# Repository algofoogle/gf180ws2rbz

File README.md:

# gf180ws2rbz: Raybox-zero supporting materials

For now, this is just a test PCB for various parts that could be used to support a raybox-zero devkit.

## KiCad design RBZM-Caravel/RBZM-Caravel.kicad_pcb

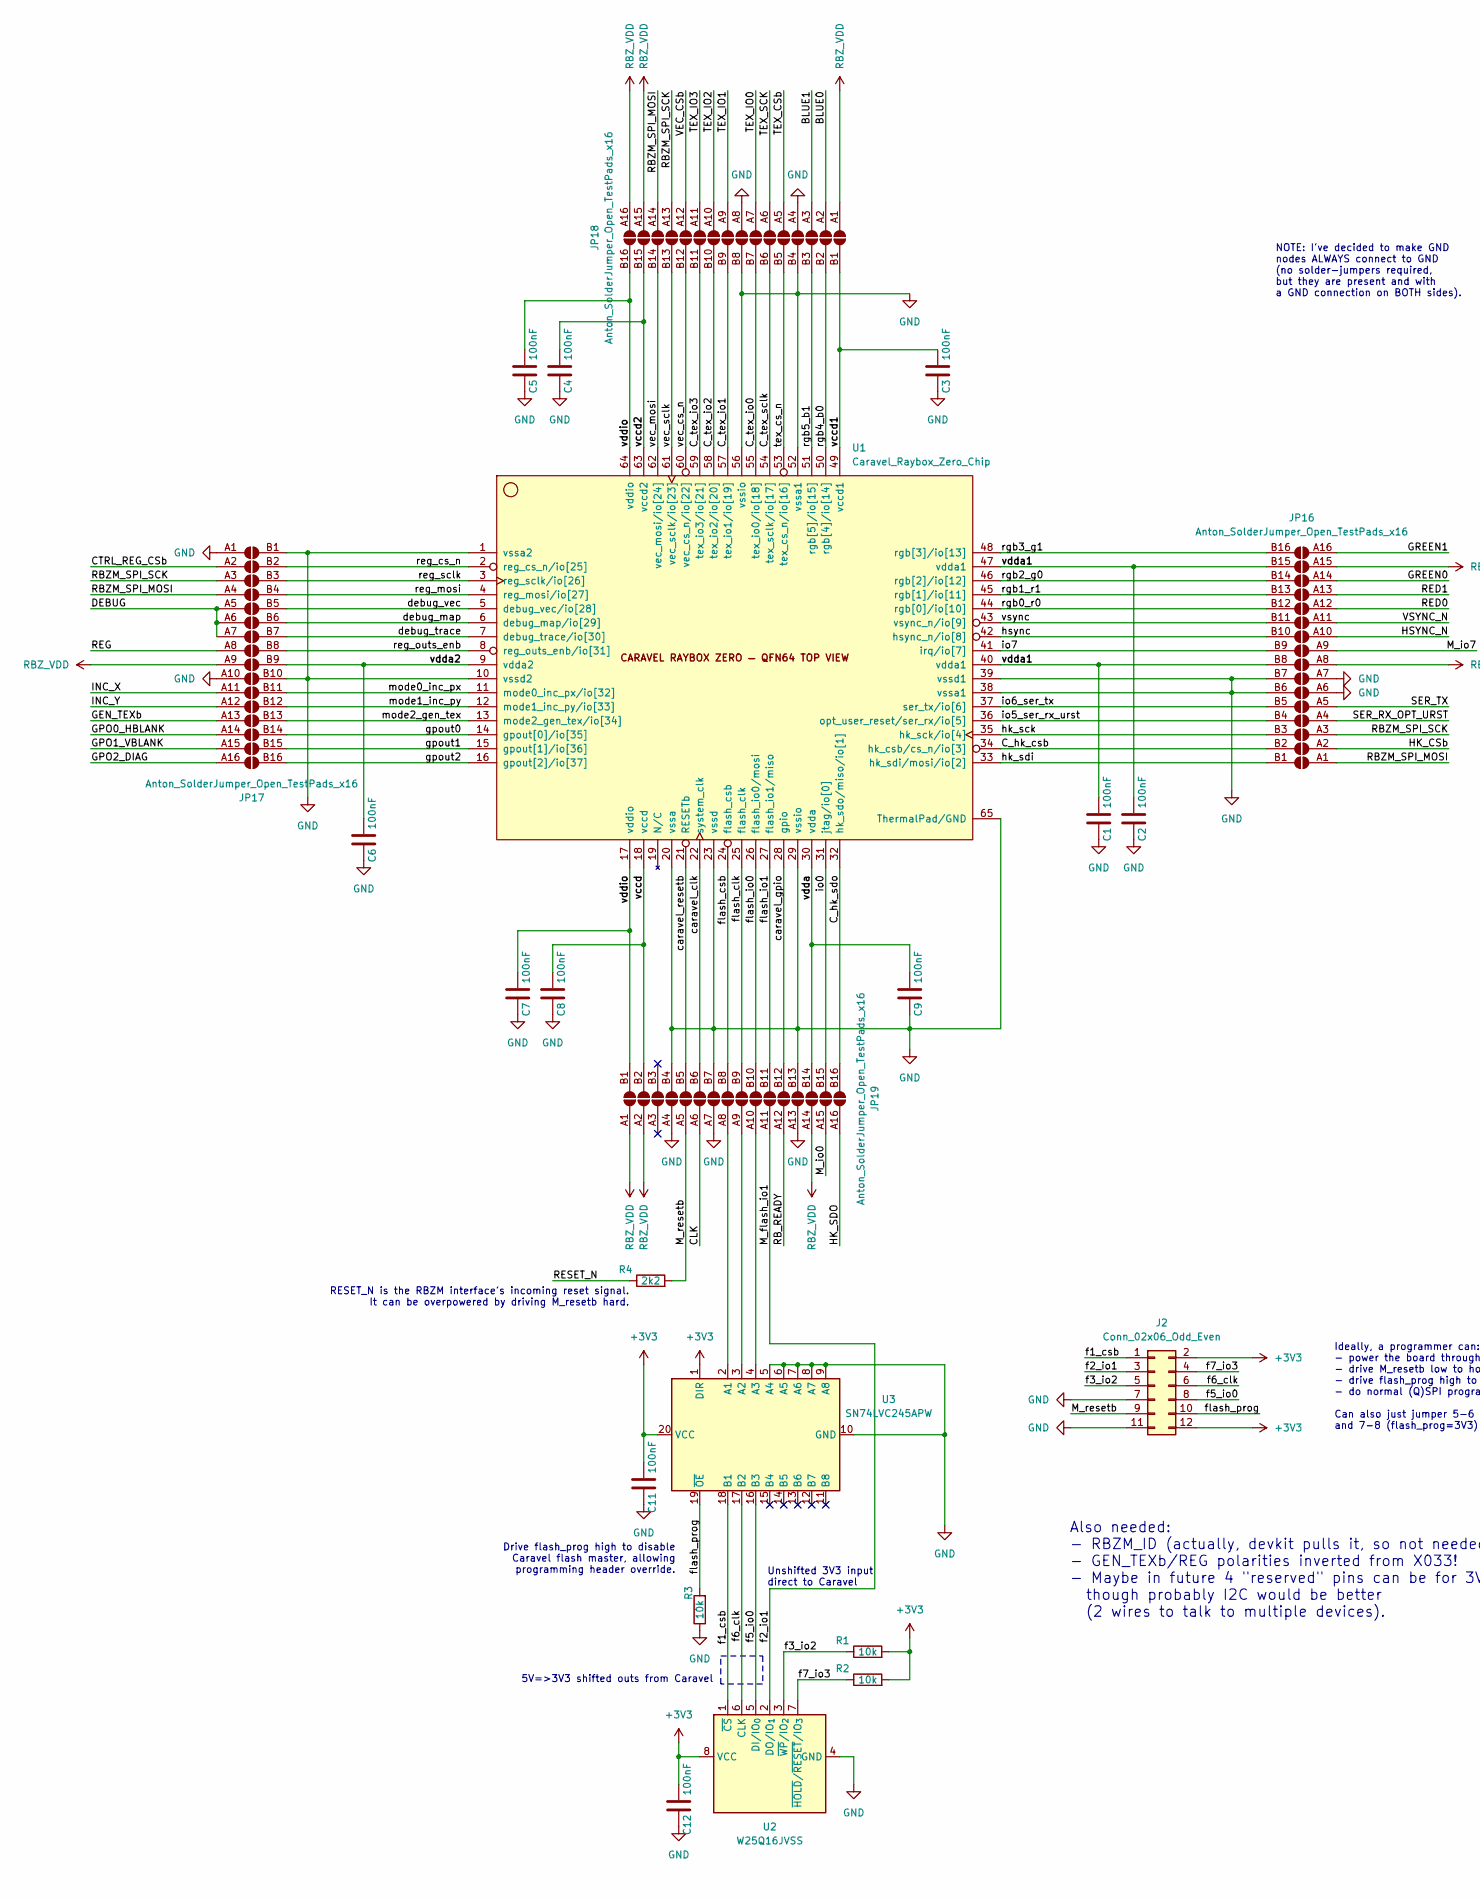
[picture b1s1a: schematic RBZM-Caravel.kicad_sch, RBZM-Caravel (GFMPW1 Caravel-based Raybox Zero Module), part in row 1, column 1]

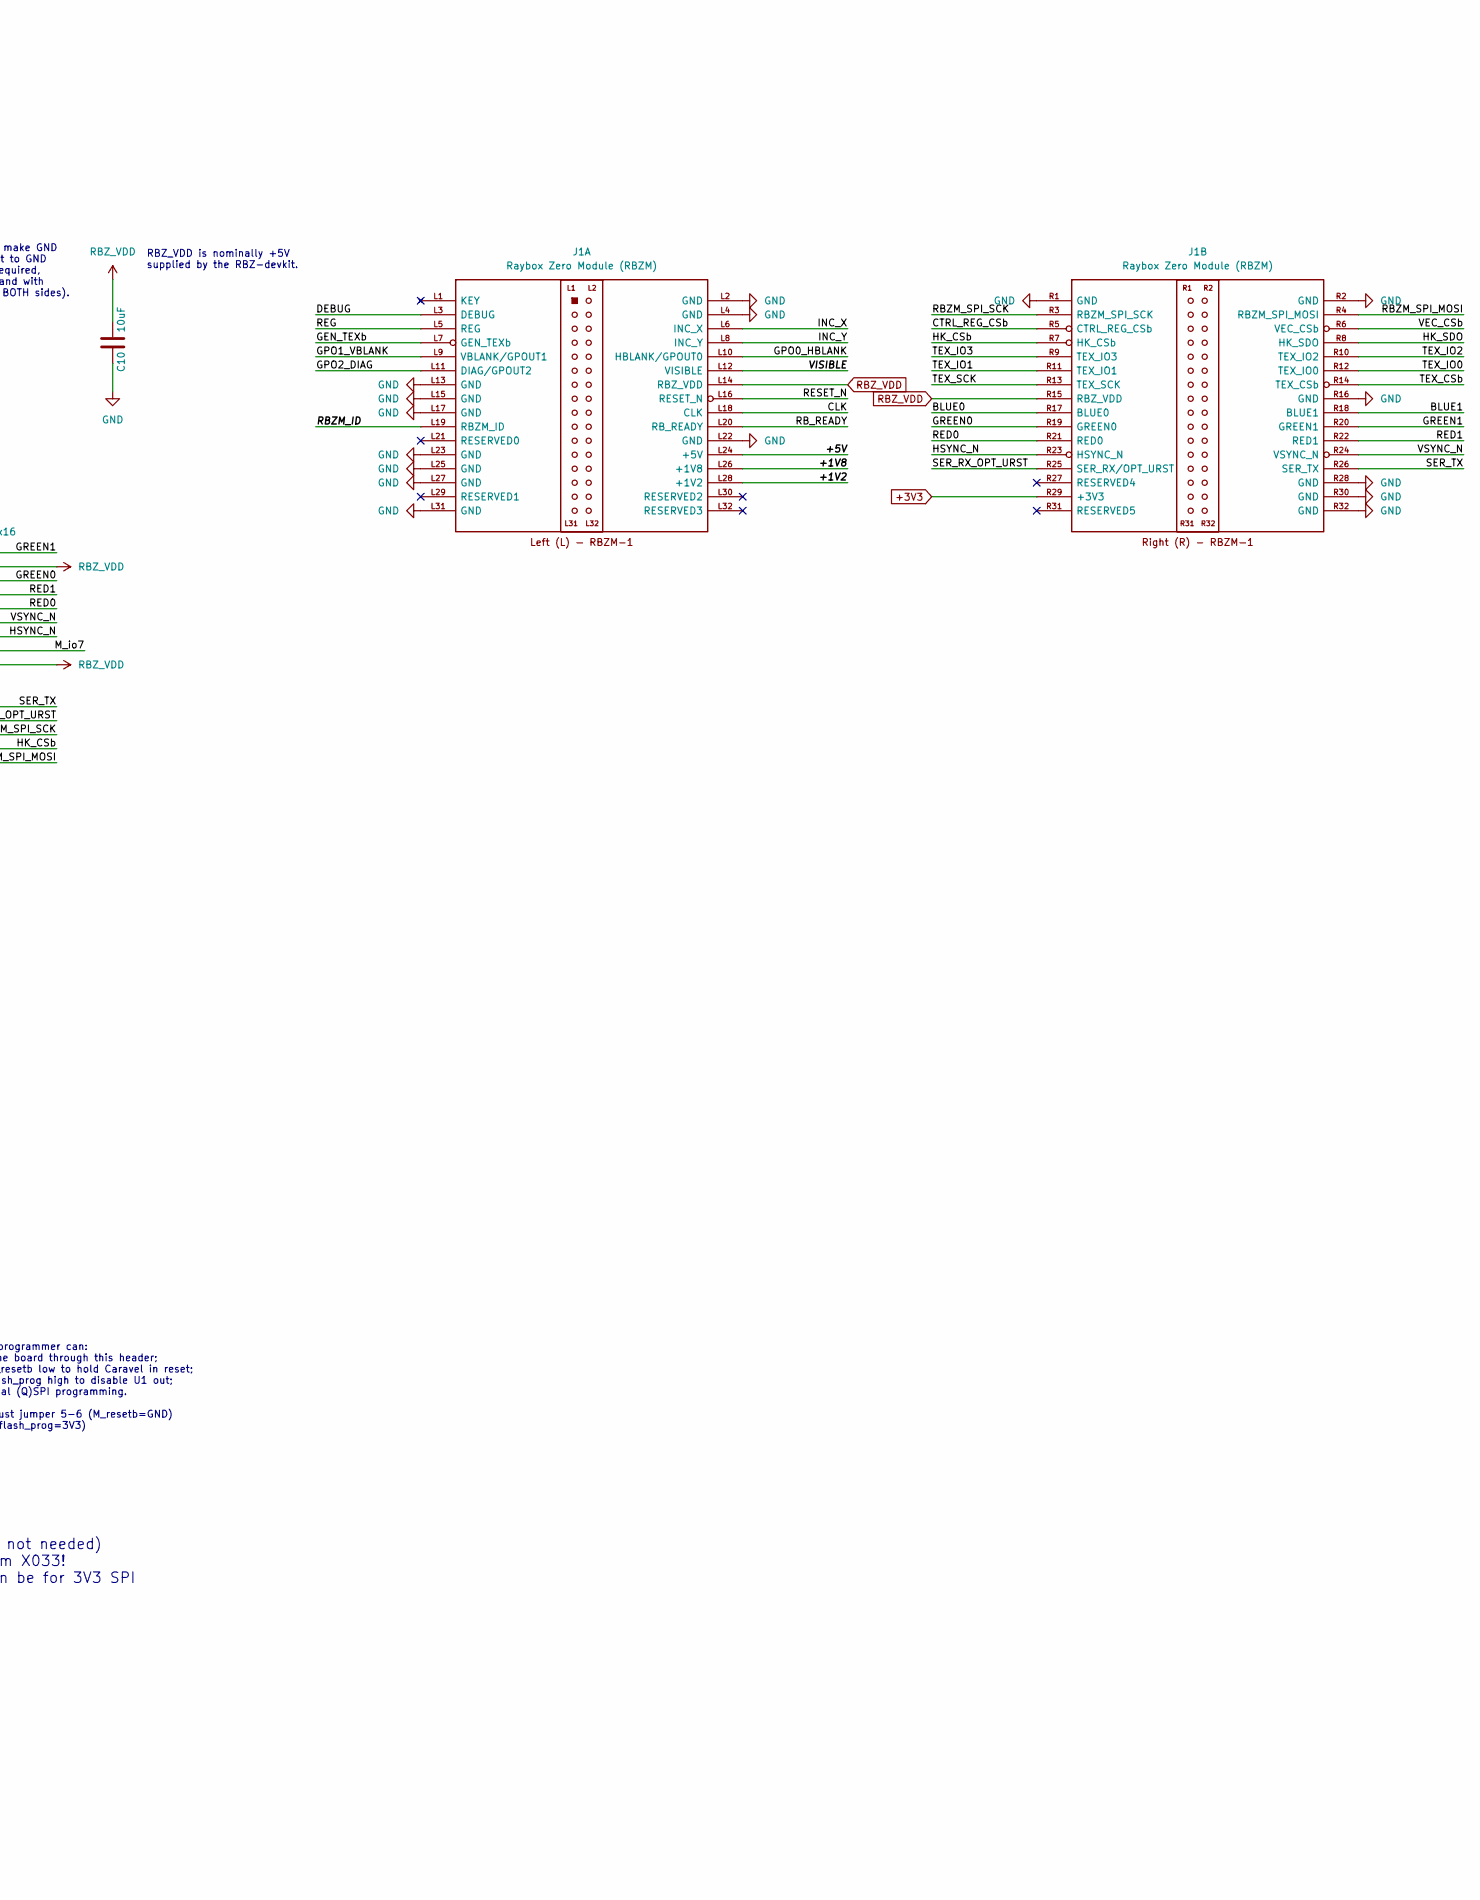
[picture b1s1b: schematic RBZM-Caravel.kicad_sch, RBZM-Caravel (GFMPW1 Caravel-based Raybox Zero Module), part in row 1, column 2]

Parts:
C1, C2, C3, C4, C5, C6, C7, C8, C9, C11, C12: 100nF; C_0603_1608Metric_Pad1.08x0.95mm_HandSolder
C10: 10uF; C_0603_1608Metric_Pad1.08x0.95mm_HandSolder
J1: Raybox Zero Module (RBZM); RBZM_Raybox_Zero_Module
J2: Conn_02x06_Odd_Even; PinHeader_2x06_P2.54mm_Vertical
JP16, JP17, JP18, JP19: Anton_SolderJumper_Open_TestPads_x16; Anton_SolderJumpers_01x16_1.27mm_Compact_SMD
R1, R2, R3: 10k; R_0603_1608Metric_Pad0.98x0.95mm_HandSolder
R4: 2k2; R_0603_1608Metric_Pad0.98x0.95mm_HandSolder
U1: Caravel_Raybox_Zero_Chip; Anton-QFN-64-1EP_9x9mm_P0.5mm_EP7.65x7.65mm-HOLE
U2: W25Q16JVSS; Anton-SOIC-8_MULTIx4.9mm_P1.27mm
U3: SN74LVC245APW; TSSOP-20_4.4x6.5mm_P0.65mm

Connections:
+3V3: C11.2, C12.2, J1.R29 (+3V3), J2.2, J2.12, R1.2, R2.2, U2.8 (VCC), U3.1 (DIR), U3.20 (VCC)
/+1V2: J1.L28 (+1V2)
/+1V8: J1.L26 (+1V8)
/+5V: J1.L24 (+5V)
/BLUE0: J1.R17 (BLUE0), JP18.A2
/BLUE1: J1.R18 (BLUE1), JP18.A3
/CLK: J1.L18 (CLK), JP19.A6
/CTRL_REG_CSb: J1.R5 (CTRL_REG_CSb), JP17.A2
/C_hk_csb: JP16.B2, U1.34 (hk_csb/cs_n/io[3])
/C_hk_sdo: JP19.B16, U1.32 (hk_sdo/miso/io[1])
/C_tex_io0: JP18.B7, U1.55 (tex_io0/io[18])
/C_tex_io1: JP18.B9, U1.57 (tex_io1/io[19])
/C_tex_io2: JP18.B10, U1.58 (tex_io2/io[20])
/C_tex_io3: JP18.B11, U1.59 (tex_io3/io[21])
/C_tex_sclk: JP18.B6, U1.54 (tex_sclk/io[17])
/DEBUG: J1.L3 (DEBUG), JP17.A5, JP17.A6, JP17.A7
/GEN_TEXb: J1.L7 (GEN_TEXb), JP17.A13
/GPO0_HBLANK: J1.L10 (HBLANK/GPOUT0), JP17.A14
/GPO1_VBLANK: J1.L9 (VBLANK/GPOUT1), JP17.A15
/GPO2_DIAG: J1.L11 (DIAG/GPOUT2), JP17.A16
/GREEN0: J1.R19 (GREEN0), JP16.A14
/GREEN1: J1.R20 (GREEN1), JP16.A16
/HK_CSb: J1.R7 (HK_CSb), JP16.A2
/HK_SDO: J1.R8 (HK_SDO), JP19.A16
/HSYNC_N: J1.R23 (HSYNC_N), JP16.A10
/INC_X: J1.L6 (INC_X), JP17.A11
/INC_Y: J1.L8 (INC_Y), JP17.A12
/M_flash_io1: J2.3, JP19.A11, U2.2 (DO/IO_{1})
/M_io0: JP19.A15
/M_io7: JP16.A9
/M_resetb: J2.9, JP19.A5, R4.2
/RBZM_ID: J1.L19 (RBZM_ID)
/RBZM_SPI_MOSI: J1.R4 (RBZM_SPI_MOSI), JP16.A1, JP17.A4, JP18.A14
/RBZM_SPI_SCK: J1.R3 (RBZM_SPI_SCK), JP16.A3, JP17.A3, JP18.A13
/RB_READY: J1.L20 (RB_READY), JP19.A12
/RED0: J1.R21 (RED0), JP16.A12
/RED1: J1.R22 (RED1), JP16.A13
/REG: J1.L5 (REG), JP17.A8
/RESET_N: J1.L16 (RESET_N), R4.1
/SER_RX_OPT_URST: J1.R25 (SER_RX/OPT_URST), JP16.A4
/SER_TX: J1.R26 (SER_TX), JP16.A5
/TEX_CSb: J1.R14 (TEX_CSb), JP18.A5
/TEX_IO0: J1.R12 (TEX_IO0), JP18.A7
/TEX_IO1: J1.R11 (TEX_IO1), JP18.A9
/TEX_IO2: J1.R10 (TEX_IO2), JP18.A10
/TEX_IO3: J1.R9 (TEX_IO3), JP18.A11
/TEX_SCK: J1.R13 (TEX_SCK), JP18.A6
/VEC_CSb: J1.R6 (VEC_CSb), JP18.A12
/VISIBLE: J1.L12 (VISIBLE)
/VSYNC_N: J1.R24 (VSYNC_N), JP16.A11
/caravel_clk: JP19.B6, U1.22 (system_clk)
/caravel_gpio: JP19.B12, U1.28 (gpio)
/caravel_resetb: JP19.B5, U1.21 (RESETb)
/debug_map: JP17.B6, U1.6 (debug_map/io[29])
/debug_trace: JP17.B7, U1.7 (debug_trace/io[30])
/debug_vec: JP17.B5, U1.5 (debug_vec/io[28])
/f1_csb: J2.1, U2.1 (~CS), U3.18 (B1)
/f3_io2: J2.5, R1.1, U2.3 (~WP/IO_{2})
/f5_io0: J2.8, U2.5 (DI/IO_{0}), U3.16 (B3)
/f6_clk: J2.6, U2.6 (CLK), U3.17 (B2)
/f7_io3: J2.4, R2.1, U2.7 (~HOLD/~RESET/IO_{3})
/flash_clk: JP19.B9, U1.25 (flash_clk)
/flash_csb: JP19.B8, U1.24 (flash_csb)
/flash_io0: JP19.B10, U1.26 (flash_io0/mosi)
/flash_io1: JP19.B11, U1.27 (flash_io1/miso)
/flash_prog: J2.10, R3.2, U3.19 (~OE)
/gpout0: JP17.B14, U1.14 (gpout[0]/io[35])
/gpout1: JP17.B15, U1.15 (gpout[1]/io[36])
/gpout2: JP17.B16, U1.16 (gpout[2]/io[37])
/hk_sck: JP16.B3, U1.35 (hk_sck/io[4])
/hk_sdi: JP16.B1, U1.33 (hk_sdi/mosi/io[2])
/hsync: JP16.B10, U1.42 (hsync_n/io[8])
/io0: JP19.B15, U1.31 (jtag/io[0])
/io5_ser_rx_urst: JP16.B4, U1.36 (opt_user_reset/ser_rx/io[5])
/io6_ser_tx: JP16.B5, U1.37 (ser_tx/io[6])
/io7: JP16.B9, U1.41 (irq/io[7])
/mode0_inc_px: JP17.B11, U1.11 (mode0_inc_px/io[32])
/mode1_inc_py: JP17.B12, U1.12 (mode1_inc_py/io[33])
/mode2_gen_tex: JP17.B13, U1.13 (mode2_gen_tex/io[34])
/reg_cs_n: JP17.B2, U1.2 (reg_cs_n/io[25])
/reg_mosi: JP17.B4, U1.4 (reg_mosi/io[27])
/reg_outs_enb: JP17.B8, U1.8 (reg_outs_enb/io[31])
/reg_sclk: JP17.B3, U1.3 (reg_sclk/io[26])
/rgb0_r0: JP16.B12, U1.44 (rgb[0]/io[10])
/rgb1_r1: JP16.B13, U1.45 (rgb[1]/io[11])
/rgb2_g0: JP16.B14, U1.46 (rgb[2]/io[12])
/rgb3_g1: JP16.B16, U1.48 (rgb[3]/io[13])
/rgb4_b0: JP18.B2, U1.50 (rgb[4]/io[14])
/rgb5_b1: JP18.B3, U1.51 (rgb[5]/io[15])
/tex_cs_n: JP18.B5, U1.53 (tex_cs_n/io[16])
/vccd: C8.2, JP19.B2, U1.18 (vccd)
/vccd1: C3.2, JP18.B1, U1.49 (vccd1)
/vccd2: C4.2, JP18.B15, U1.63 (vccd2)
/vdda: C9.2, JP19.B14, U1.30 (vdda)
/vdda1: C1.2, C2.2, JP16.B8, JP16.B15, U1.40 (vdda1), U1.47 (vdda1)
/vdda2: C6.2, JP17.B9, U1.9 (vdda2)
/vddio: C5.2, C7.2, JP18.B16, JP19.B1, U1.17 (vddio), U1.64 (vddio)
/vec_cs_n: JP18.B12, U1.60 (vec_cs_n/io[22])
/vec_mosi: JP18.B14, U1.62 (vec_mosi/io[24])
/vec_sclk: JP18.B13, U1.61 (vec_sclk/io[23])
/vsync: JP16.B11, U1.43 (vsync_n/io[9])
GND: C1.1, C2.1, C3.1, C4.1, C5.1, C6.1, C7.1, C8.1, C9.1, C10.1, C11.1, C12.1, J1.L2 (GND), J1.L4 (GND), J1.L13 (GND), J1.L15 (GND), J1.L17 (GND), J1.L22 (GND), J1.L23 (GND), J1.L25 (GND), J1.L27 (GND), J1.L31 (GND), J1.R1 (GND), J1.R2 (GND), J1.R16 (GND), J1.R28 (GND), J1.R30 (GND), J1.R32 (GND), J2.7, J2.11, JP16.A6, JP16.A7, JP16.B6, JP16.B7, JP17.A1, JP17.A10, JP17.B1, JP17.B10, JP18.A4, JP18.A8, JP18.B4, JP18.B8, JP19.A4, JP19.A7, JP19.A13, JP19.B4, JP19.B7, JP19.B13, R3.1, U1.1 (vssa2), U1.10 (vssd2), U1.20 (vssa), U1.23 (vssd), U1.29 (vssio), U1.38 (vssa1), U1.39 (vssd1), U1.52 (vssa1), U1.56 (vssio), U1.65 (ThermalPad/GND), U2.4 (GND), U3.5 (A4), U3.6 (A5), U3.7 (A6), U3.8 (A7), U3.9 (A8), U3.10 (GND)
unnamed: JP19.A8, U3.2 (A1)
unnamed: JP19.A9, U3.3 (A2)
unnamed: JP19.A10, U3.4 (A3)
RBZ_VDD: C10.2, J1.L14 (RBZ_VDD), J1.R15 (RBZ_VDD), JP16.A8, JP16.A15, JP17.A9, JP18.A1, JP18.A15, JP18.A16, JP19.A1, JP19.A2, JP19.A14

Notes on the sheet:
NOTE: I've decided to make GND nodes ALWAYS connect to GND (no solder-jumpers required, but they are present and with a GND connection on BOTH sides).
Drive flash_prog high to disable Caravel flash master, allowing programming header override.
RESET_N is the RBZM interface's incoming reset signal. It can be overpowered by driving M_resetb hard.
Ideally, a programmer can: - power the board through this header; - drive M_resetb low to hold Caravel in reset; - drive flash_prog high to disable U1 out; - do normal (Q)SPI programming. Can also just jumper 5-6 (M_resetb=GND) and 7-8 (flash_prog=3V3)
Also needed: - RBZM_ID (actually, devkit pulls it, so not needed) - GEN_TEXb/REG polarities inverted from X033! - Maybe in future 4 "reserved" pins can be for 3V3 SPI though probably I2C would be better (2 wires to talk to multiple devices).
5V=>3V3 shifted outs from Caravel
Unshifted 3V3 input direct to Caravel
RBZ_VDD is nominally +5V supplied by the RBZ-devkit.

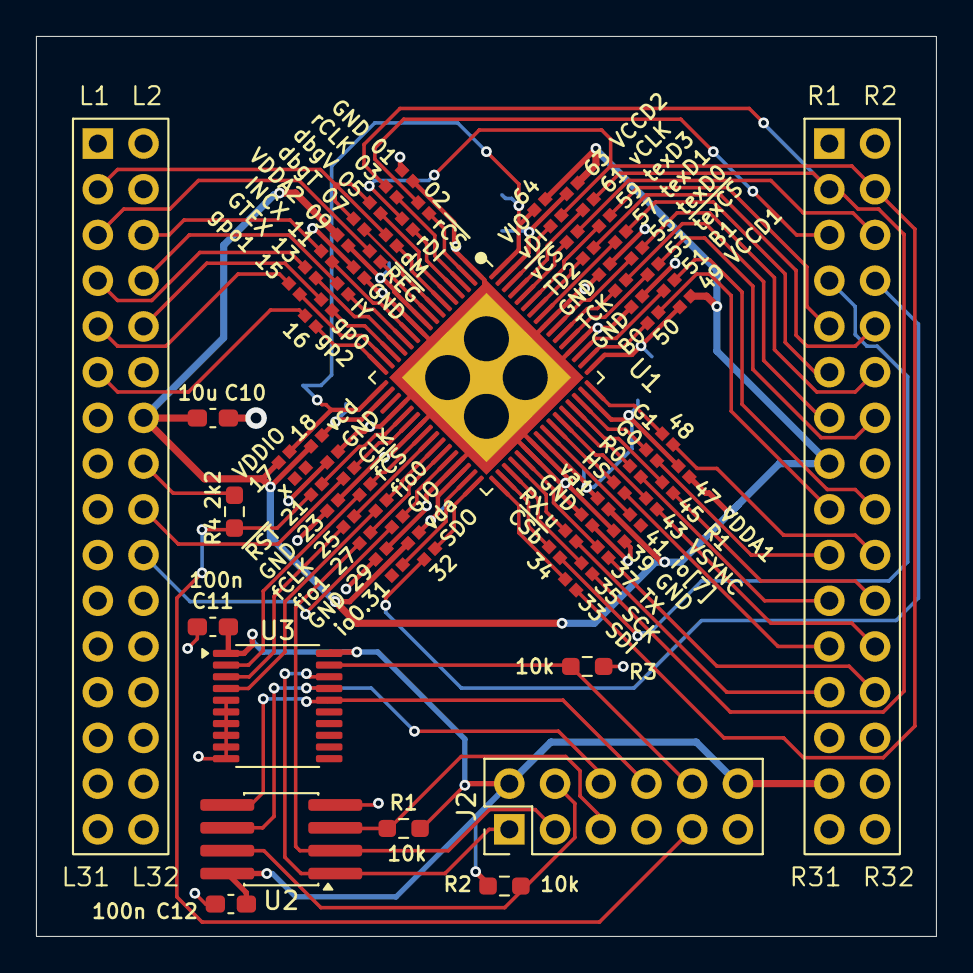
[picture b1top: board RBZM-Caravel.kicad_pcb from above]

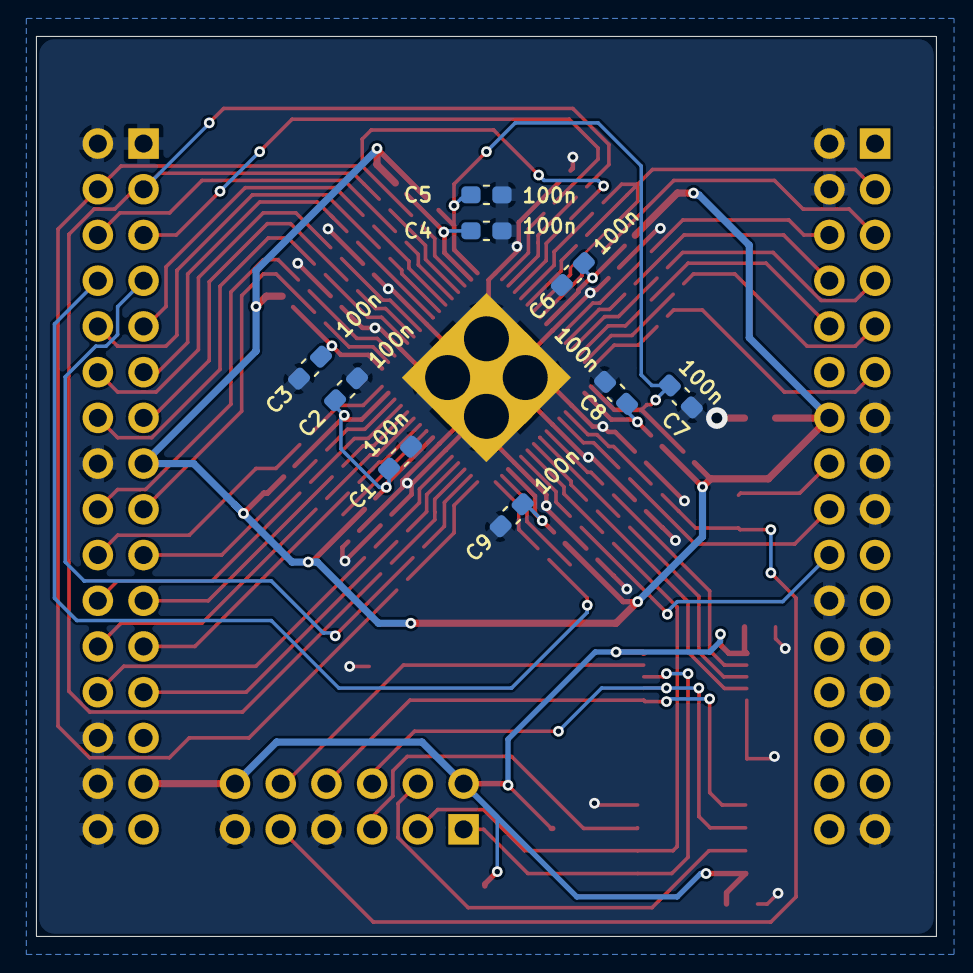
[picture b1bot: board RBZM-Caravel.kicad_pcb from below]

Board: 2 copper layers, 50.0 x 50.0 mm, 25 parts (9 on the bottom side), 99 nets.

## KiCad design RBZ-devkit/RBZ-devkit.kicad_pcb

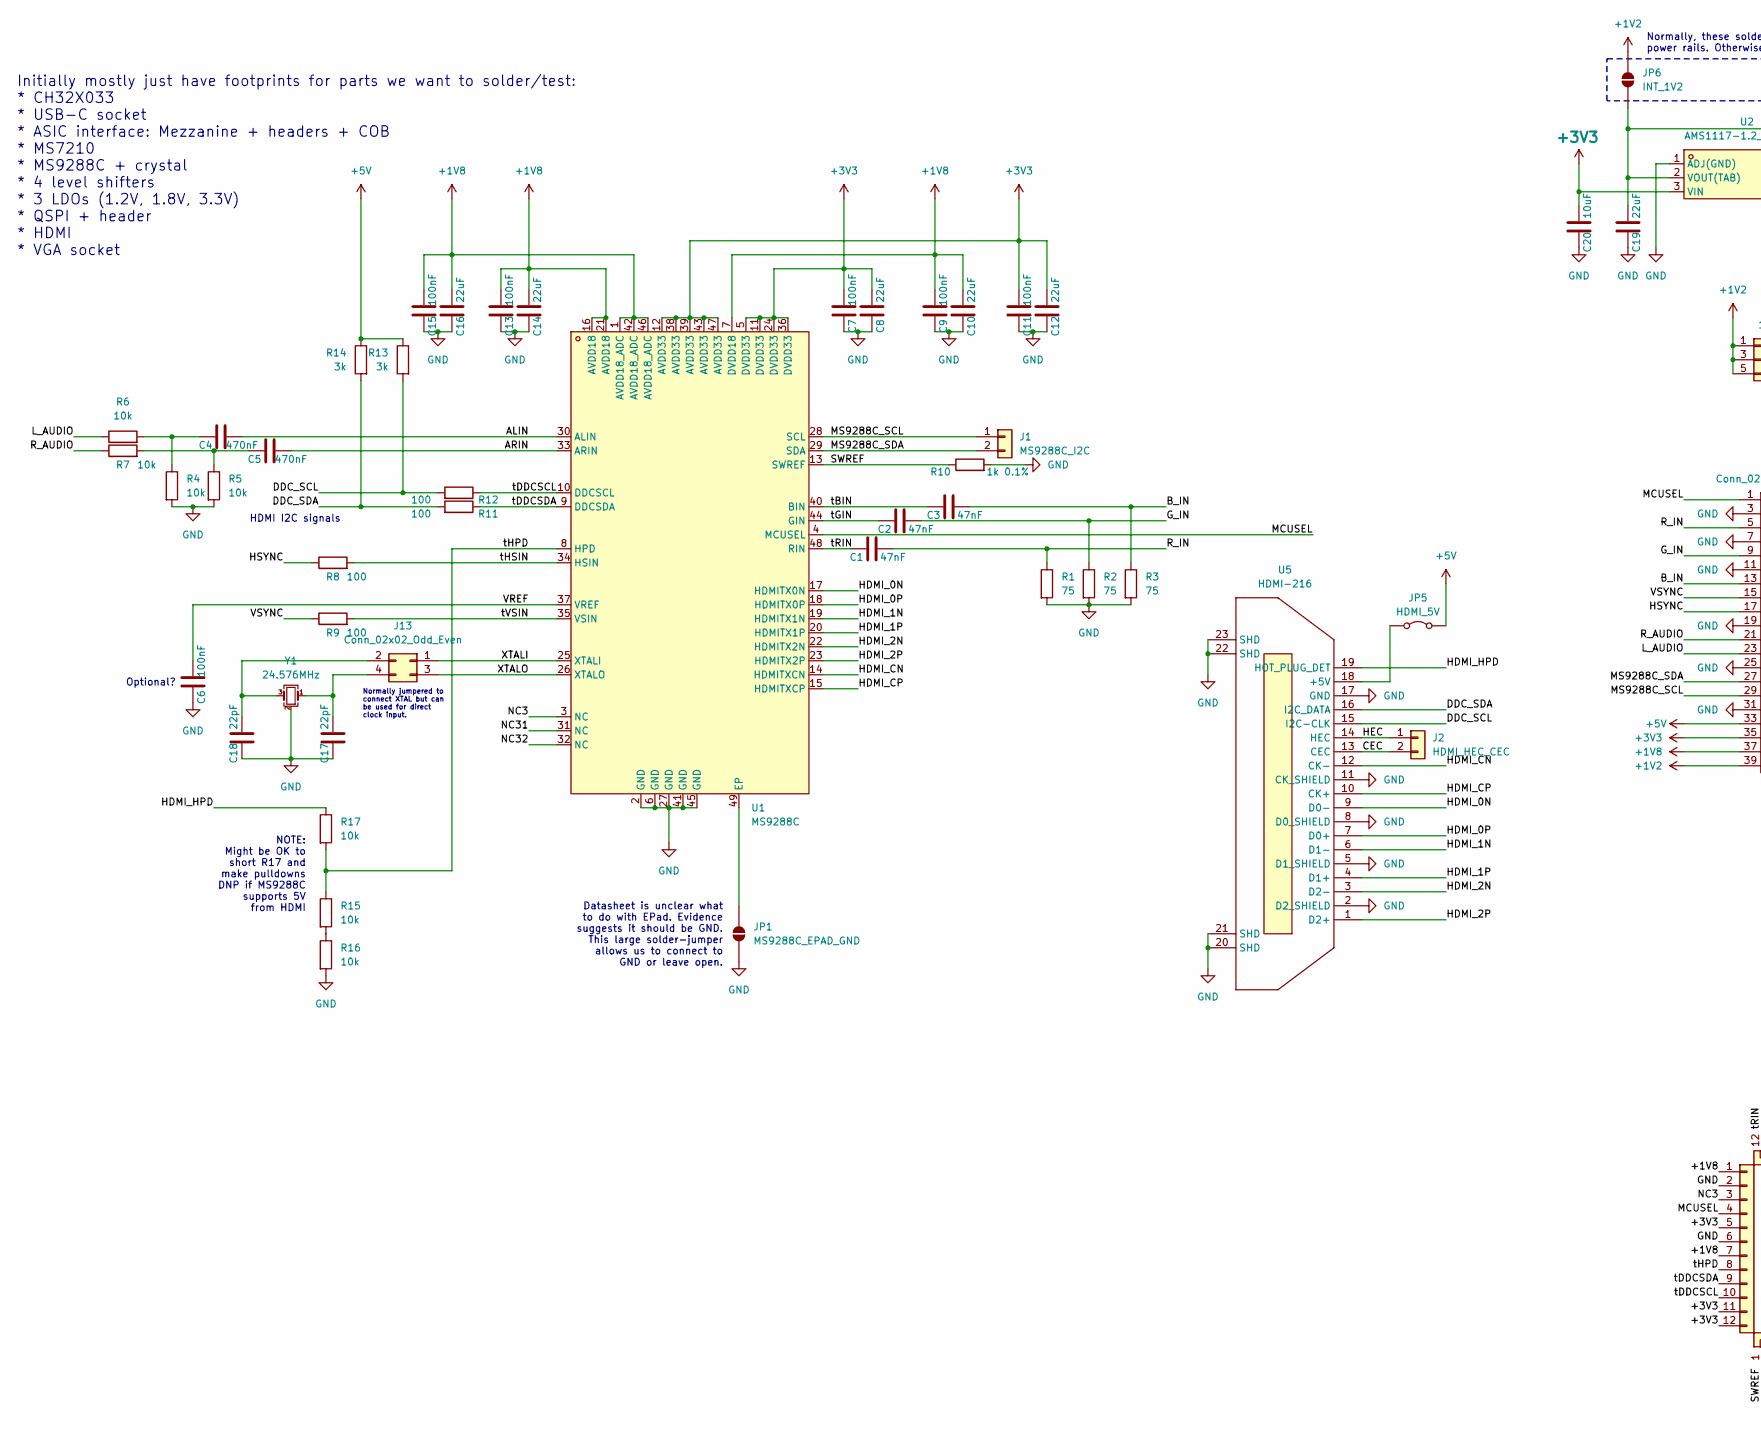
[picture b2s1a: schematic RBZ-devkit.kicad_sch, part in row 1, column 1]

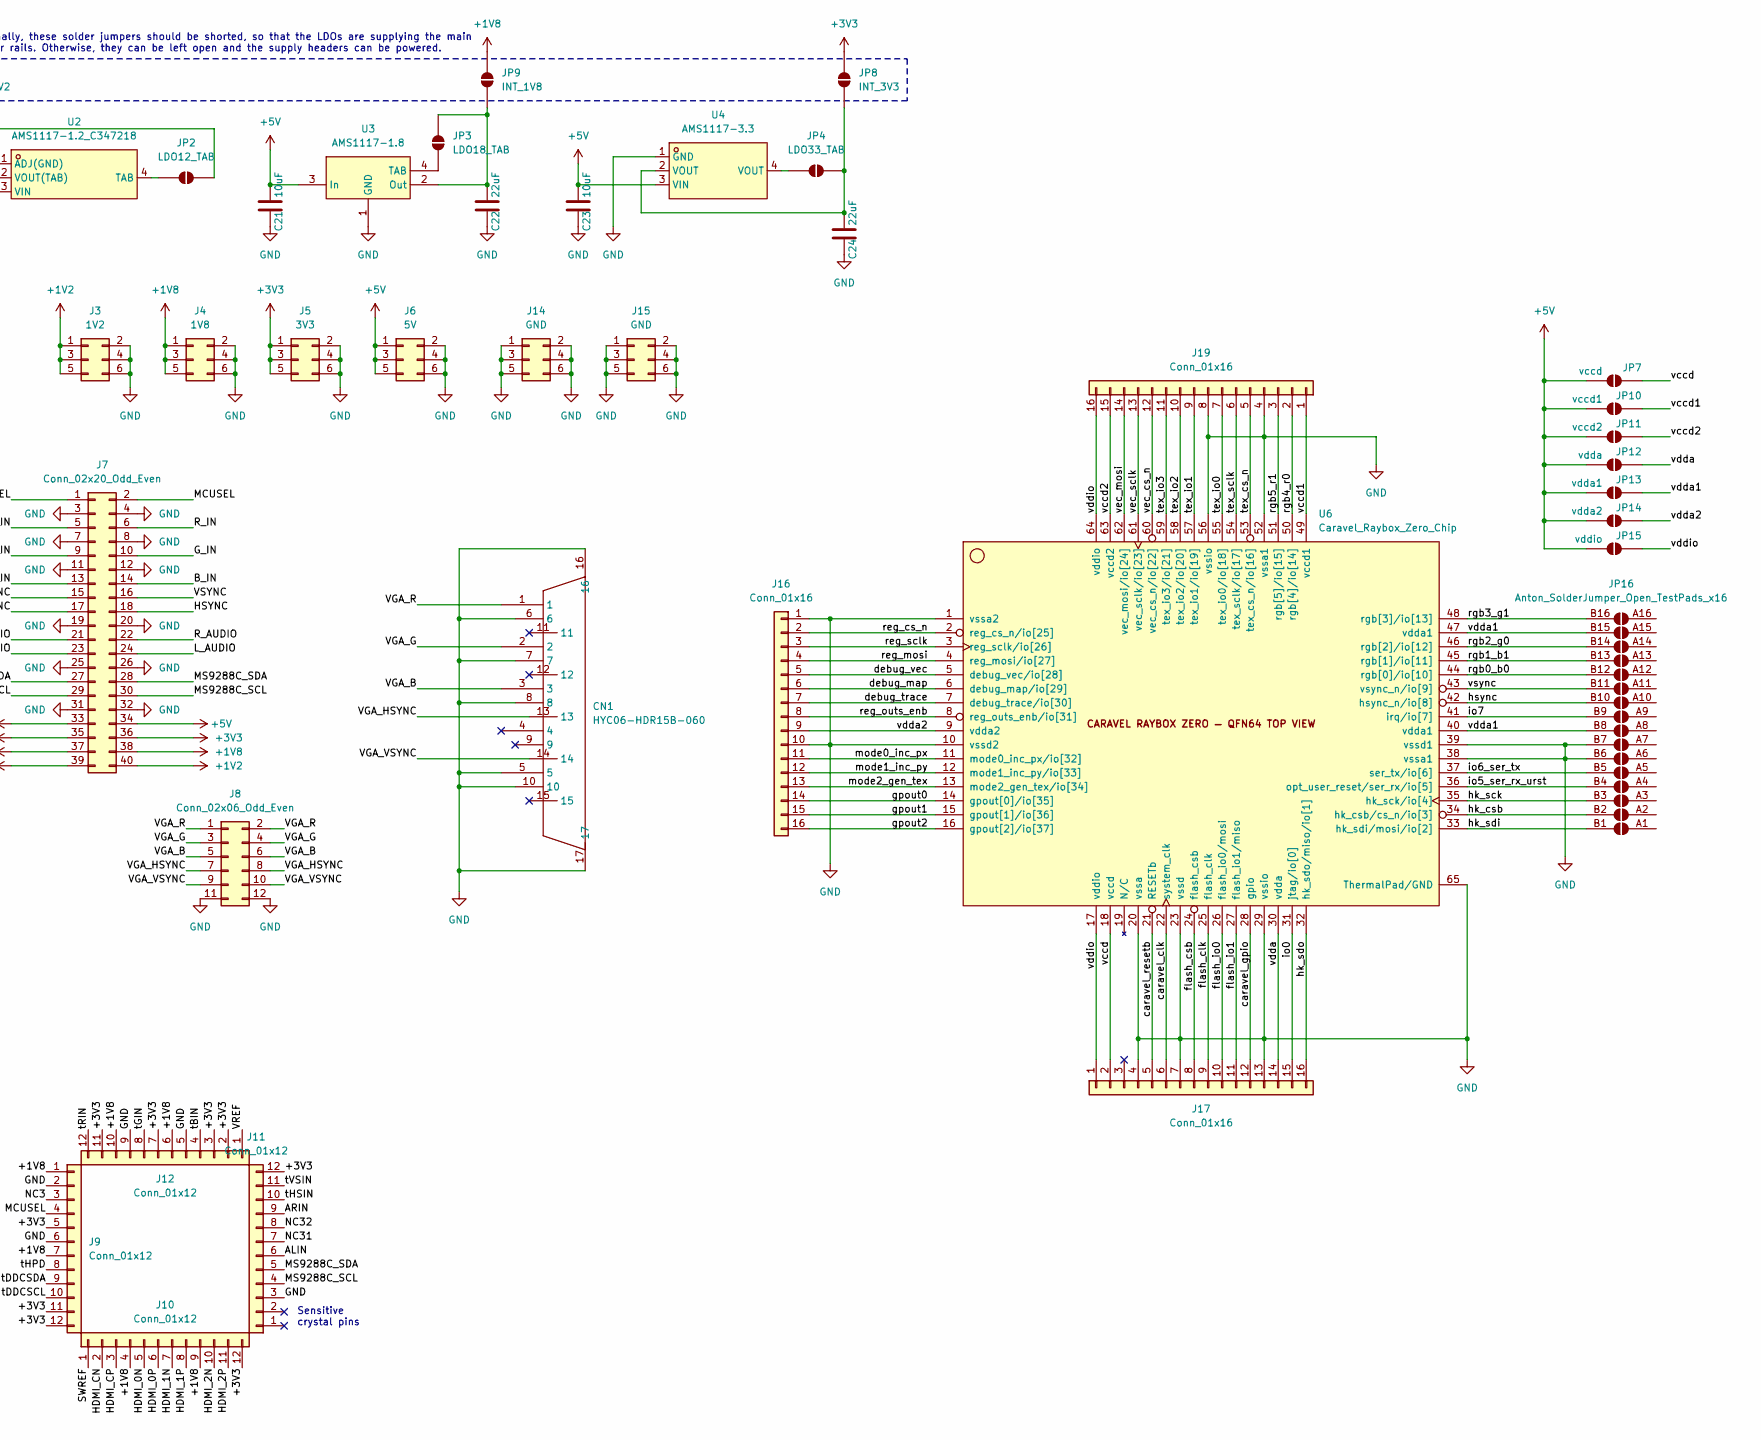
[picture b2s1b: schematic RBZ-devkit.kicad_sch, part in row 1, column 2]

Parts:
C1, C2, C3: 47nF; C_0603_1608Metric_Pad1.08x0.95mm_HandSolder
C4, C5: 470nF; C_0603_1608Metric_Pad1.08x0.95mm_HandSolder
C6, C7, C9, C11, C13, C15: 100nF; C_0603_1608Metric_Pad1.08x0.95mm_HandSolder
C8, C10, C12, C14, C16, C19, C22, C24: 22uF; C_0603_1608Metric_Pad1.08x0.95mm_HandSolder
C17, C18: 22pF; C_0603_1608Metric_Pad1.08x0.95mm_HandSolder
C20, C21, C23: 10uF; C_0603_1608Metric_Pad1.08x0.95mm_HandSolder
CN1: HYC06-HDR15B-060; DSUB-TH_HYC06-HDR15B-060; MPN HYC06-HDR15B-060; LCSC Part C711364
J1: MS9288C_I2C; PinHeader_1x02_P2.54mm_Vertical
J2: HDMI_HEC_CEC; PinHeader_1x02_P2.54mm_Vertical
J3: 1V2; PinHeader_2x03_P2.54mm_Vertical
J4: 1V8; PinHeader_2x03_P2.54mm_Vertical
J5: 3V3; PinHeader_2x03_P2.54mm_Vertical
J6: 5V; PinHeader_2x03_P2.54mm_Vertical
J7: Conn_02x20_Odd_Even; PinHeader_2x20_P2.54mm_Vertical
J8: Conn_02x06_Odd_Even; PinHeader_2x06_P2.54mm_Vertical
J9, J10, J11, J12: Conn_01x12; AntonPTHTestPointStagger12way
J13: Conn_02x02_Odd_Even; Anton-PinSocket_2x02_P2.54mm_Vertical-SolderJumper
J14, J15: GND; PinHeader_2x03_P2.54mm_Vertical
J16, J17, J19: Conn_01x16; Anton_Pads_01x16_1.27mm_Compact_SMD
JP1: MS9288C_EPAD_GND; SolderJumper-2_P1.3mm_Open_RoundedPad1.0x1.5mm
JP2: LDO12_TAB; SolderJumper-2_P1.3mm_Open_RoundedPad1.0x1.5mm
JP3: LDO18_TAB; SolderJumper-2_P1.3mm_Open_RoundedPad1.0x1.5mm
JP4: LDO33_TAB; SolderJumper-2_P1.3mm_Open_RoundedPad1.0x1.5mm
JP5: HDMI_5V; Anton-PinHeader_1x02_P2.54mm_Vertical-SolderJumper
JP6: INT_1V2; SolderJumper-2_P1.3mm_Open_RoundedPad1.0x1.5mm
JP7: vccd; SolderJumper-2_P1.3mm_Open_RoundedPad1.0x1.5mm
JP8: INT_3V3; SolderJumper-2_P1.3mm_Open_RoundedPad1.0x1.5mm
JP9: INT_1V8; SolderJumper-2_P1.3mm_Open_RoundedPad1.0x1.5mm
JP10: vccd1; SolderJumper-2_P1.3mm_Open_RoundedPad1.0x1.5mm
JP11: vccd2; SolderJumper-2_P1.3mm_Open_RoundedPad1.0x1.5mm
JP12: vdda; SolderJumper-2_P1.3mm_Open_RoundedPad1.0x1.5mm
JP13: vdda1; SolderJumper-2_P1.3mm_Open_RoundedPad1.0x1.5mm
JP14: vdda2; SolderJumper-2_P1.3mm_Open_RoundedPad1.0x1.5mm
JP15: vddio; SolderJumper-2_P1.3mm_Open_RoundedPad1.0x1.5mm
JP16: Anton_SolderJumper_Open_TestPads_x16; Anton_SolderJumpers_01x16_1.27mm_Compact_SMD
R1, R2, R3: 75; R_0603_1608Metric_Pad0.98x0.95mm_HandSolder
R4, R5, R6, R7, R15, R16, R17: 10k; R_0603_1608Metric_Pad0.98x0.95mm_HandSolder
R8, R9, R11, R12: 100; R_0603_1608Metric_Pad0.98x0.95mm_HandSolder
R10: 1k 0.1%; R_0603_1608Metric_Pad0.98x0.95mm_HandSolder
R13, R14: 3k; R_0603_1608Metric_Pad0.98x0.95mm_HandSolder
U1: MS9288C; Anton-QFN-48_L6-W6-P0.4-TL-EP4.2-HandSolder; MPN MS9288C; LCSC Part C2914316
U2: AMS1117-1.2_C347218; SOT-223_L6.7-W3.5-P2.30-BR; MPN AMS1117-1.2; LCSC Part C347218
U3: AMS1117-1.8; SOT-223-4_L6.5-W3.5-P2.30-LS7.0-BR; MPN AMS1117-1.8; LCSC Part C6185
U4: AMS1117-3.3; SOT-223-3_L6.5-W3.4-P2.30-LS7.0-BR; MPN AMS1117-3.3; LCSC Part C6186
U5: HDMI-216; HDMI-SMD_KH-HDMI-19P-CU; MPN HDMI-216; LCSC Part C2962407
U6: Caravel_Raybox_Zero_Chip; Anton-QFN-64-1EP_9x9mm_P0.5mm_EP7.65x7.65mm-HOLE
Y1: 24.576MHz; Crystal_SMD_EuroQuartz_MT-4Pin_3.2x2.5mm_HandSoldering; PartNum XTM32024576JT00351001; LCSC_PartNum C41383247

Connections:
+1V2: J3.1, J3.3, J3.5, J7.39, J7.40, JP6.1 (A)
+1V8: C9.2, C10.2, C13.2, C14.2, C15.2, C16.2, J4.1, J4.3, J4.5, J7.37, J7.38, J9.1, J9.7, J10.4, J10.9, J12.6, J12.10, JP9.1 (A), U1.1 (AVDD18_ADC), U1.7 (DVDD18), U1.16 (AVDD18), U1.21 (AVDD18), U1.42 (AVDD18_ADC), U1.46 (AVDD18_ADC)
+3V3: C7.2, C8.2, C11.2, C12.2, C20.2, J5.1, J5.3, J5.5, J7.35, J7.36, J9.5, J9.11, J9.12, J10.12, J11.12, J12.2, J12.3, J12.7, J12.11, JP8.1 (A), U1.5 (DVDD33), U1.11 (DVDD33), U1.12 (AVDD33), U1.24 (DVDD33), U1.36 (DVDD33), U1.38 (AVDD33), U1.39 (AVDD33), U1.43 (AVDD33), U1.47 (AVDD33), U2.3 (VIN)
+5V: C21.2, C23.2, J6.1, J6.3, J6.5, J7.33, J7.34, JP5.2 (B), JP7.2 (B), JP10.2 (B), JP11.2 (B), JP12.2 (B), JP13.2 (B), JP14.2 (B), JP15.2 (B), R13.1, R14.1, U3.3 (In), U4.3 (VIN); also elsewhere on the board
/ALIN: C4.2, J11.6, U1.30 (ALIN)
/ARIN: C5.2, J11.9, U1.33 (ARIN)
/B_IN: C3.2, J7.13, J7.14, R3.1
/CEC: J2.2, U5.13 (CEC)
/DDC_SCL: R12.2, R13.2, U5.15 (I2C-CLK)
/DDC_SDA: R11.2, R14.2, U5.16 (I2C_DATA)
/G_IN: C2.2, J7.9, J7.10, R2.1
/HDMI_0N: J10.5, U1.17 (HDMITX0N), U5.9 (D0-)
/HDMI_0P: J10.6, U1.18 (HDMITX0P), U5.7 (D0+)
/HDMI_1N: J10.7, U1.19 (HDMITX1N), U5.6 (D1-)
/HDMI_1P: J10.8, U1.20 (HDMITX1P), U5.4 (D1+)
/HDMI_2N: J10.10, U1.22 (HDMITX2N), U5.3 (D2-)
/HDMI_2P: J10.11, U1.23 (HDMITX2P), U5.1 (D2+)
/HDMI_CN: J10.2, U1.14 (HDMITXCN), U5.12 (CK-)
/HDMI_CP: J10.3, U1.15 (HDMITXCP), U5.10 (CK+)
/HDMI_HPD: R17.1, U5.19 (HOT_PLUG_DET)
/HEC: J2.1, U5.14 (HEC)
/HSYNC: J7.17, J7.18, R8.1; also elsewhere on the board
/L_AUDIO: J7.23, J7.24, R6.1
/MCUSEL: J7.1, J7.2, J9.4, U1.4 (MCUSEL)
/MS9288C_SCL: J1.1, J7.29, J7.30, J11.4, U1.28 (SCL)
/MS9288C_SDA: J1.2, J7.27, J7.28, J11.5, U1.29 (SDA)
/NC3: J9.3, U1.3 (NC)
/NC31: J11.7, U1.31 (NC)
/NC32: J11.8, U1.32 (NC)
/R_AUDIO: J7.21, J7.22, R7.1
/R_IN: C1.2, J7.5, J7.6, R1.1
/SWREF: J10.1, R10.1, U1.13 (SWREF)
/VGA_B: CN1.3, J8.5, J8.6
/VGA_G: CN1.2, J8.3, J8.4
/VGA_HSYNC: CN1.13, J8.7, J8.8; also elsewhere on the board
/VGA_R: CN1.1, J8.1, J8.2
/VGA_VSYNC: CN1.14, J8.9, J8.10; also elsewhere on the board
/VREF: C6.2, J12.1, U1.37 (VREF)
/VSYNC: J7.15, J7.16, R9.1; also elsewhere on the board
/XTALI: J13.1, U1.25 (XTALI)
/XTALO: J13.3, U1.26 (XTALO)
/caravel_clk: J17.6, U6.22 (system_clk)
/caravel_gpio: J17.12, U6.28 (gpio)
/caravel_resetb: J17.5, U6.21 (RESETb)
/debug_map: J16.6, U6.6 (debug_map/io[29])
/debug_trace: J16.7, U6.7 (debug_trace/io[30])
/debug_vec: J16.5, U6.5 (debug_vec/io[28])
/flash_clk: J17.9, U6.25 (flash_clk)
/flash_csb: J17.8, U6.24 (flash_csb)
/flash_io0: J17.10, U6.26 (flash_io0/mosi)
/flash_io1: J17.11, U6.27 (flash_io1/miso)
/gpout0: J16.14, U6.14 (gpout[0]/io[35])
/gpout1: J16.15, U6.15 (gpout[1]/io[36])
/gpout2: J16.16, U6.16 (gpout[2]/io[37])
/hk_csb: JP16.B2, U6.34 (hk_csb/cs_n/io[3])
/hk_sck: JP16.B3, U6.35 (hk_sck/io[4])
/hk_sdi: JP16.B1, U6.33 (hk_sdi/mosi/io[2])
/hk_sdo: J17.16, U6.32 (hk_sdo/miso/io[1])
/hsync: JP16.B10, U6.42 (hsync_n/io[8])
/io0: J17.15, U6.31 (jtag/io[0])
/io5_ser_rx_urst: JP16.B4, U6.36 (opt_user_reset/ser_rx/io[5])
/io6_ser_tx: JP16.B5, U6.37 (ser_tx/io[6])
/io7: JP16.B9, U6.41 (irq/io[7])
/mode0_inc_px: J16.11, U6.11 (mode0_inc_px/io[32])
/mode1_inc_py: J16.12, U6.12 (mode1_inc_py/io[33])
/mode2_gen_tex: J16.13, U6.13 (mode2_gen_tex/io[34])
/reg_cs_n: J16.2, U6.2 (reg_cs_n/io[25])
/reg_mosi: J16.4, U6.4 (reg_mosi/io[27])
/reg_outs_enb: J16.8, U6.8 (reg_outs_enb/io[31])
/reg_sclk: J16.3, U6.3 (reg_sclk/io[26])
/rgb0_b0: JP16.B12, U6.44 (rgb[0]/io[10])
/rgb1_b1: JP16.B13, U6.45 (rgb[1]/io[11])
/rgb2_g0: JP16.B14, U6.46 (rgb[2]/io[12])
/rgb3_g1: JP16.B16, U6.48 (rgb[3]/io[13])
/rgb4_r0: J19.2, U6.50 (rgb[4]/io[14])
/rgb5_r1: J19.3, U6.51 (rgb[5]/io[15])
/tBIN: C3.1, J12.4, U1.40 (BIN)
/tDDCSCL: J9.10, R12.1, U1.10 (DDCSCL)
/tDDCSDA: J9.9, R11.1, U1.9 (DDCSDA)
/tGIN: C2.1, J12.8, U1.44 (GIN)
/tHPD: J9.8, R15.1, R17.2, U1.8 (HPD)
/tHSIN: J11.10, R8.2, U1.34 (HSIN)
/tRIN: C1.1, J12.12, U1.48 (RIN)
/tVSIN: J11.11, R9.2, U1.35 (VSIN)
/tex_cs_n: J19.5, U6.53 (tex_cs_n/io[16])
/tex_io0: J19.7, U6.55 (tex_io0/io[18])
/tex_io1: J19.9, U6.57 (tex_io1/io[19])
/tex_io2: J19.10, U6.58 (tex_io2/io[20])
/tex_io3: J19.11, U6.59 (tex_io3/io[21])
/tex_sclk: J19.6, U6.54 (tex_sclk/io[17])
/vccd: J17.2, JP7.1 (A), U6.18 (vccd); also elsewhere on the board
/vccd1: J19.1, JP10.1 (A), U6.49 (vccd1); also elsewhere on the board
/vccd2: J19.15, JP11.1 (A), U6.63 (vccd2); also elsewhere on the board
/vdda: J17.14, JP12.1 (A), U6.30 (vdda)
/vdda1: JP13.1 (A), JP16.B8, JP16.B15, U6.40 (vdda1), U6.47 (vdda1)
/vdda2: J16.9, JP14.1 (A), U6.9 (vdda2)
/vddio: J17.1, J19.16, JP15.1 (A), U6.17 (vddio), U6.64 (vddio)
/vec_cs_n: J19.12, U6.60 (vec_cs_n/io[22])
/vec_mosi: J19.14, U6.62 (vec_mosi/io[24])
/vec_sclk: J19.13, U6.61 (vec_sclk/io[23])
/vsync: JP16.B11, U6.43 (vsync_n/io[9])
GND: C6.1, C7.1, C8.1, C9.1, C10.1, C11.1, C12.1, C13.1, C14.1, C15.1, C16.1, C17.1, C18.1, C19.1, C20.1, C21.1, C22.1, C23.1, C24.1, CN1.5, CN1.6, CN1.7, CN1.8, CN1.10, CN1.16, CN1.17, J3.2, J3.4, J3.6, J4.2, J4.4, J4.6, J5.2, J5.4, J5.6, J6.2, J6.4, J6.6, J7.3, J7.4, J7.7, J7.8, J7.11, J7.12, J7.19, J7.20, J7.25, J7.26, J7.31, J7.32, J8.11, J8.12, J9.2, J9.6, J11.3, J12.5, J12.9, J14.1, J14.2, J14.3, J14.4, J14.5, J14.6, J15.1, J15.2, J15.3, J15.4, J15.5, J15.6, J16.1, J16.10, J17.4, J17.7, J17.13, J19.4, J19.8, JP1.1 (A), JP16.B6, JP16.B7, R1.2, R2.2, R3.2, R4.2, R5.2, R10.2, R16.2, U1.2 (GND), U1.6 (GND), U1.27 (GND), U1.41 (GND), U1.45 (GND), U2.1 (ADJ(GND)), U3.1 (GND), U4.1 (GND), U5.2 (D2_SHIELD), U5.5 (D1_SHIELD), U5.8 (D0_SHIELD), U5.11 (CK_SHIELD), U5.17 (GND), U5.20 (SHD), U5.21 (SHD), U5.22 (SHD), U5.23 (SHD), U6.1 (vssa2), U6.10 (vssd2), U6.20 (vssa), U6.23 (vssd), U6.29 (vssio), U6.38 (vssa1), U6.39 (vssd1), U6.52 (vssa1), U6.56 (vssio), U6.65 (ThermalPad/GND), Y1.2 (G), Y1.4 (G)
unnamed: C4.1, R4.1, R6.2
unnamed: C5.1, R5.1, R7.2
unnamed: C18.2, J13.2, Y1.3
unnamed: C17.2, J13.4, Y1.1
unnamed: JP1.2 (B), U1.49 (EP)
unnamed: C19.2, JP2.1 (A), JP6.2 (B), U2.2 (VOUT(TAB))
unnamed: JP2.2 (B), U2.4 (TAB)
unnamed: C22.2, JP3.1 (A), JP9.2 (B), U3.2 (Out)
unnamed: JP3.2 (B), U3.4 (TAB)
unnamed: C24.2, JP4.1 (A), JP8.2 (B), U4.2 (VOUT)
unnamed: JP4.2 (B), U4.4 (VOUT)
unnamed: JP5.1 (A), U5.18 (+5V)
unnamed: R15.2, R16.1

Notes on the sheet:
Normally, these solder jumpers should be shorted, so that the LDOs are supplying the main power rails. Otherwise, they can be left open and the supply headers can be powered.
Normally jumpered to connect XTAL but can be used for direct clock input.
Sensitive crystal pins
Optional?
Datasheet is unclear what to do with EPad. Evidence suggests it should be GND. This large solder-jumper allows us to connect to GND or leave open.
HDMI I2C signals
Initially mostly just have footprints for parts we want to solder/test: * CH32X033 * USB-C socket * ASIC interface: Mezzanine + headers + COB * MS7210 * MS9288C + crystal * 4 level shifters * 3 LDOs (1.2V, 1.8V, 3.3V) * QSPI + header * HDMI * VGA socket
NOTE: Might be OK to short R17 and make pulldowns DNP if MS9288C supports 5V from HDMI
